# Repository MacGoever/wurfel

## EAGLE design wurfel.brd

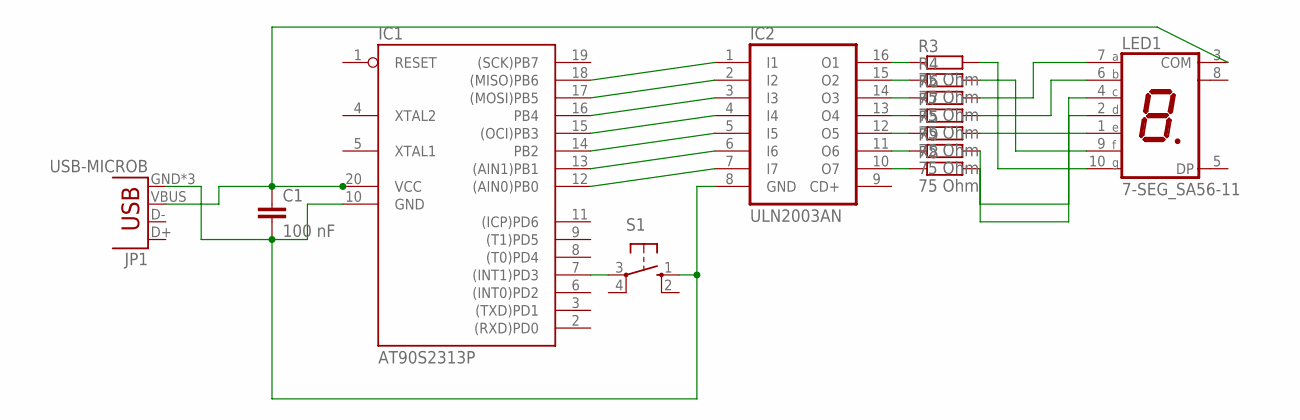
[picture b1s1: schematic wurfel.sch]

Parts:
C1: 100 nF; C050-025X075
IC1: AT90S2313P; DIL20
IC2: ULN2003AN; DIL16
JP1: USB-MICROB
LED1: 7-SEG_SA56-11; SA56-11
R3, R4, R5, R6, R7, R8, R9: 75 Ohm; 0207/10
S1: 10-XX; B3F-10XX

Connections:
GND: C1.2, IC1.10 (GND), IC2.8 (GND), JP1.GND, JP1.MT1 (GND), JP1.MT2 (GND), S1.1 (S)
unnamed: IC1.12 ((AIN0)PB0), IC2.7 (I7)
unnamed: IC1.13 ((AIN1)PB1), IC2.6 (I6)
unnamed: IC1.14 (PB2), IC2.5 (I5)
unnamed: IC1.15 ((OCI)PB3), IC2.4 (I4)
unnamed: IC1.16 (PB4), IC2.3 (I3)
unnamed: IC1.17 ((MOSI)PB5), IC2.2 (I2)
unnamed: IC1.18 ((MISO)PB6), IC2.1 (I1)
unnamed: IC1.7 ((INT1)PD3), S1.3
unnamed: LED1.10 (G), R3.2
unnamed: IC2.16 (O1), R3.1
unnamed: IC2.15 (O2), R4.1
unnamed: IC2.14 (O3), R6.1
unnamed: IC2.13 (O4), R7.1
unnamed: IC2.12 (O5), R5.1
unnamed: IC2.11 (O6), R9.1
unnamed: IC2.10 (O7), R8.1
unnamed: LED1.9 (F), R4.2
unnamed: LED1.7 (A), R6.2
unnamed: LED1.6 (B), R7.2
unnamed: LED1.4 (C), R5.2
unnamed: LED1.1 (E), R8.2
unnamed: LED1.2 (D), R9.2
VCC: C1.1, IC1.20 (VCC), JP1.VBUS, LED1.3 (COM)

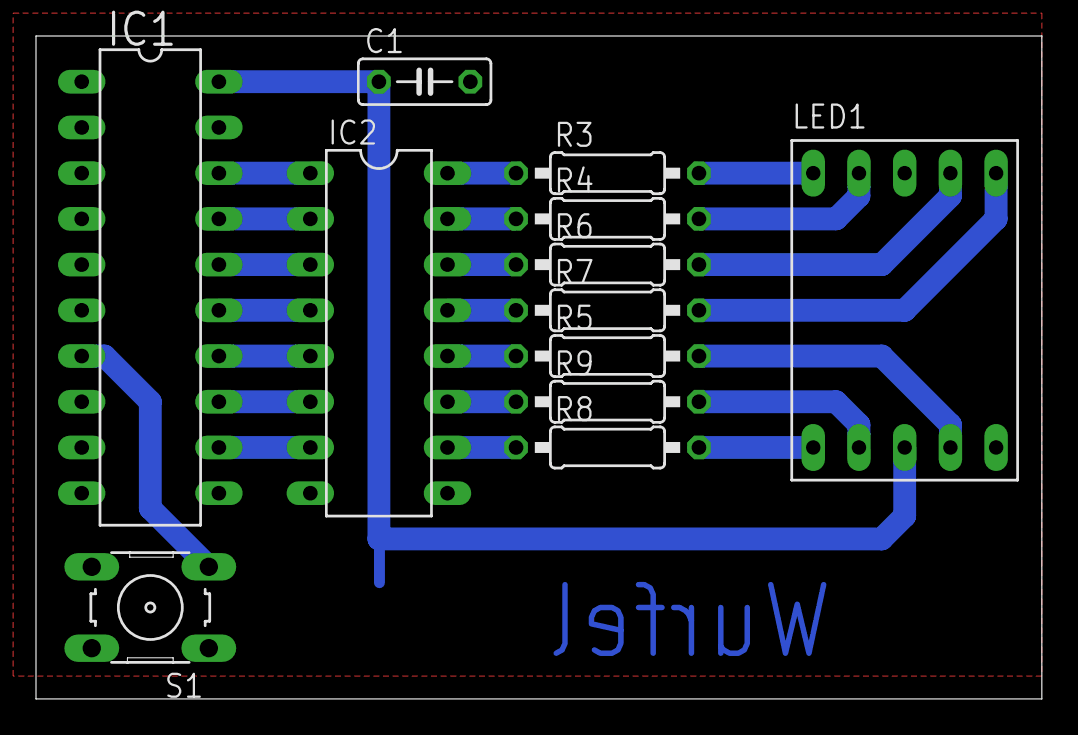
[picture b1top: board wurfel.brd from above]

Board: 2 copper layers, 55.9 x 36.8 mm, 13 parts (1 on the bottom side), 24 nets.

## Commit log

2018-01-13 Probably stable version...

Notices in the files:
parts and their libraries:
SparkFun-Connectors: Licensing: Creative Commons ShareAlike 4.0 International - https://creativecommons.org/licenses/by-sa/4.0
